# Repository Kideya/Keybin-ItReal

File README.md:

# Keybin-ItReal
A repo for sharing my keyboard designs with the world. Disclaimer: Use at your own risk!

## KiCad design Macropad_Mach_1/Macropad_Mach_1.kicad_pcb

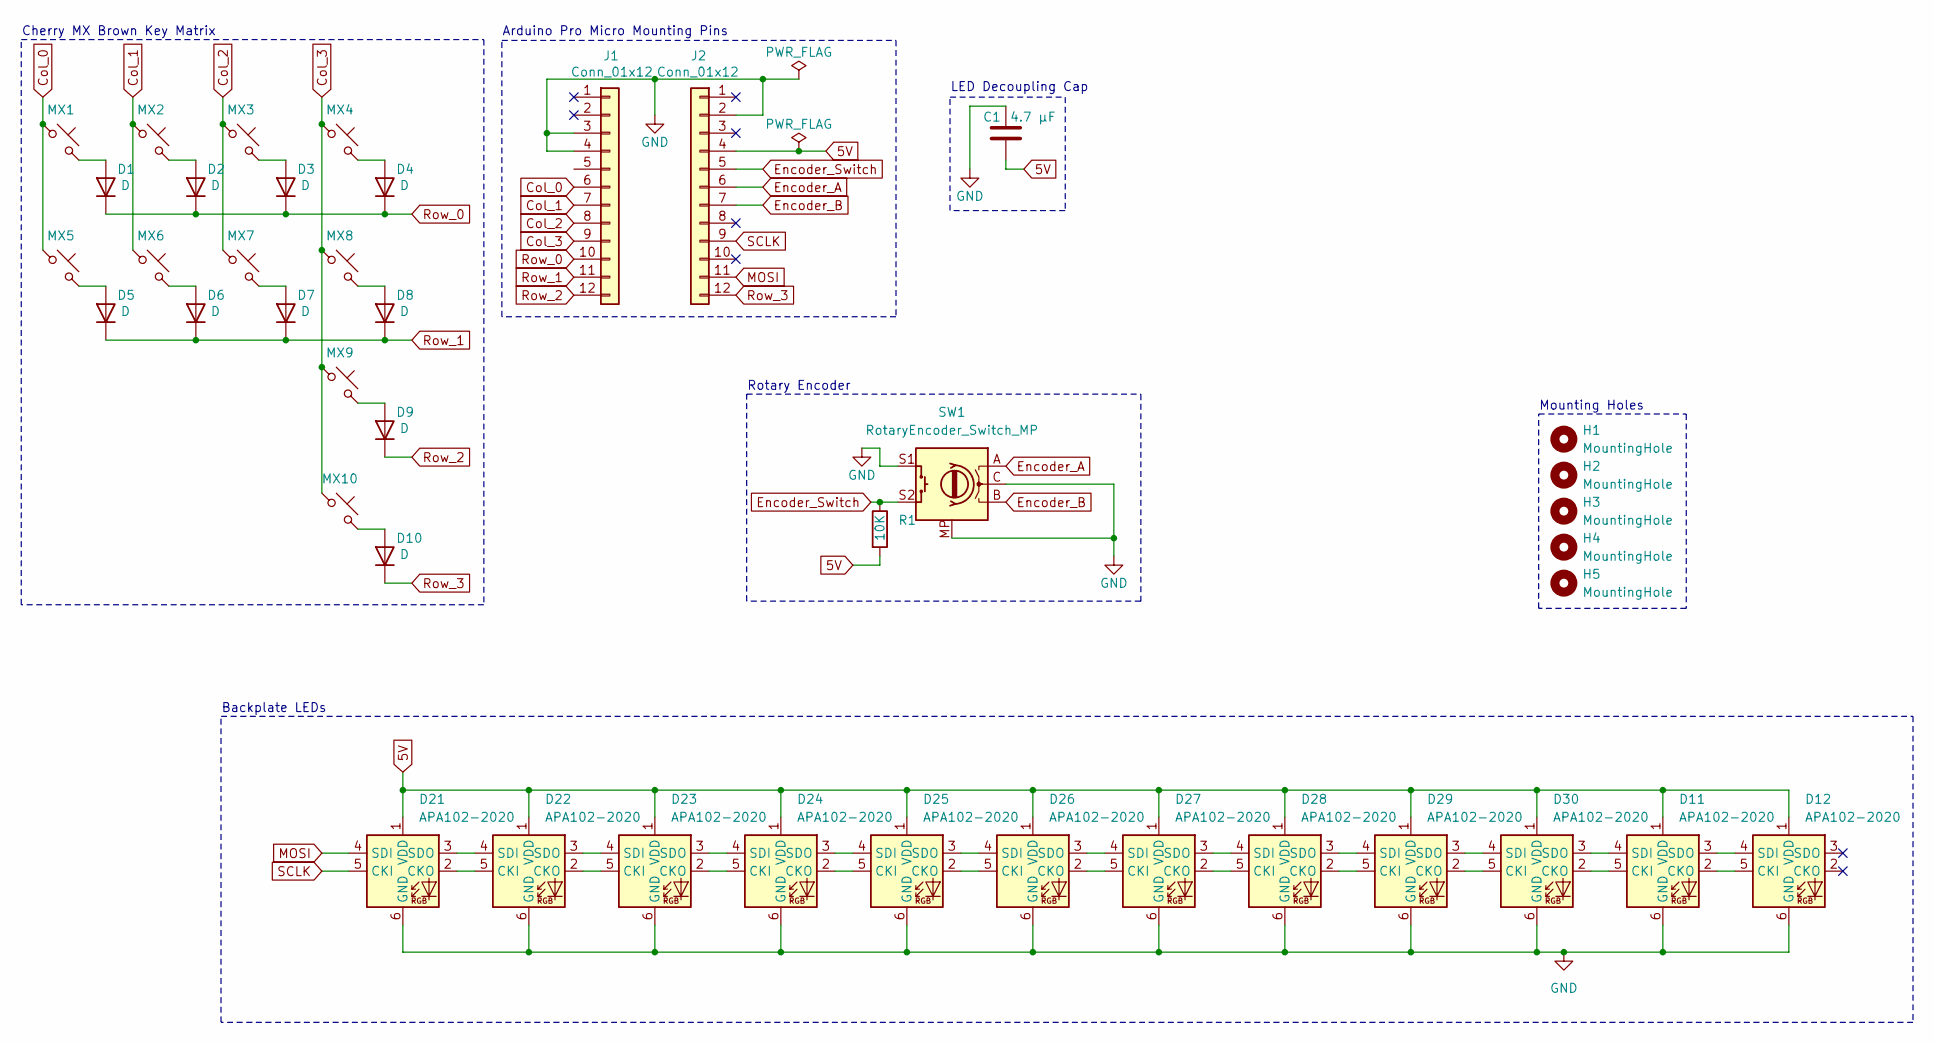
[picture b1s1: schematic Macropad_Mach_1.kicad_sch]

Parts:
C1: 4.7 µF; C_0201_0603Metric_Pad0.64x0.40mm_HandSolder
D1, D2, D3, D4, D5, D6, D7, D8, D9, D10: D; D_A-405_P7.62mm_Horizontal
D11, D12, D21, D22, D23, D24, D25, D26, D27, D28, D29, D30: APA102-2020; LED-APA102-2020
H1, H2, H3, H4, H5: MountingHole; MountingHole_3.2mm_M3
J1, J2: Conn_01x12; PinHeader_1x12_P2.54mm_Vertical
MX1, MX2, MX3, MX4, MX5, MX6, MX7, MX8, MX9, MX10: MX_SW_solder; SW_MX_1u
R1: 10K; R_0603_1608Metric_Pad0.98x0.95mm_HandSolder
SW1: RotaryEncoder_Switch_MP; RotaryEncoder_Alps_EC12E-Switch_Vertical_H20mm

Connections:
5V: C1.2, D11.1 (VDD), D12.1 (VDD), D21.1 (VDD), D22.1 (VDD), D23.1 (VDD), D24.1 (VDD), D25.1 (VDD), D26.1 (VDD), D27.1 (VDD), D28.1 (VDD), D29.1 (VDD), D30.1 (VDD), J2.4, R1.2
Col_0: J1.6, MX1.1, MX5.1
Col_1: J1.7, MX2.1, MX6.1
Col_2: J1.8, MX3.1, MX7.1
Col_3: J1.9, MX4.1, MX8.1, MX9.1, MX10.1
Encoder_A: J2.6, SW1.A
Encoder_B: J2.7, SW1.B
Encoder_Switch: J2.5, R1.1, SW1.S2
GND: C1.1, D11.6 (GND), D12.6 (GND), D21.6 (GND), D22.6 (GND), D23.6 (GND), D24.6 (GND), D25.6 (GND), D26.6 (GND), D27.6 (GND), D28.6 (GND), D29.6 (GND), D30.6 (GND), J1.3, J1.4, J2.2, SW1.C, SW1.MP, SW1.S1
MOSI: D21.4 (SDI), J2.11
unnamed: D1.2 (A), MX1.2
unnamed: D2.2 (A), MX2.2
unnamed: D3.2 (A), MX3.2
unnamed: D4.2 (A), MX4.2
unnamed: D5.2 (A), MX5.2
unnamed: D6.2 (A), MX6.2
unnamed: D7.2 (A), MX7.2
unnamed: D8.2 (A), MX8.2
unnamed: D9.2 (A), MX9.2
unnamed: D10.2 (A), MX10.2
unnamed: D11.5 (CKI), D30.2 (CKO)
unnamed: D11.2 (CKO), D12.5 (CKI)
unnamed: D11.4 (SDI), D30.3 (SDO)
unnamed: D11.3 (SDO), D12.4 (SDI)
unnamed: D21.2 (CKO), D22.5 (CKI)
unnamed: D21.3 (SDO), D22.4 (SDI)
unnamed: D22.2 (CKO), D23.5 (CKI)
unnamed: D22.3 (SDO), D23.4 (SDI)
unnamed: D23.2 (CKO), D24.5 (CKI)
unnamed: D23.3 (SDO), D24.4 (SDI)
unnamed: D24.2 (CKO), D25.5 (CKI)
unnamed: D24.3 (SDO), D25.4 (SDI)
unnamed: D25.2 (CKO), D26.5 (CKI)
unnamed: D25.3 (SDO), D26.4 (SDI)
unnamed: D26.2 (CKO), D27.5 (CKI)
unnamed: D26.3 (SDO), D27.4 (SDI)
unnamed: D27.2 (CKO), D28.5 (CKI)
unnamed: D27.3 (SDO), D28.4 (SDI)
unnamed: D28.2 (CKO), D29.5 (CKI)
unnamed: D28.3 (SDO), D29.4 (SDI)
unnamed: D29.2 (CKO), D30.5 (CKI)
unnamed: D29.3 (SDO), D30.4 (SDI)
Row_0: D1.1 (K), D2.1 (K), D3.1 (K), D4.1 (K), J1.10
Row_1: D5.1 (K), D6.1 (K), D7.1 (K), D8.1 (K), J1.11
Row_2: D9.1 (K), J1.12
Row_3: D10.1 (K), J2.12
SCLK: D21.5 (CKI), J2.9

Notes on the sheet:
Arduino Pro Micro Mounting Pins
Backplate LEDs
Cherry MX Brown Key Matrix
Mounting Holes
LED Decoupling Cap
Rotary Encoder

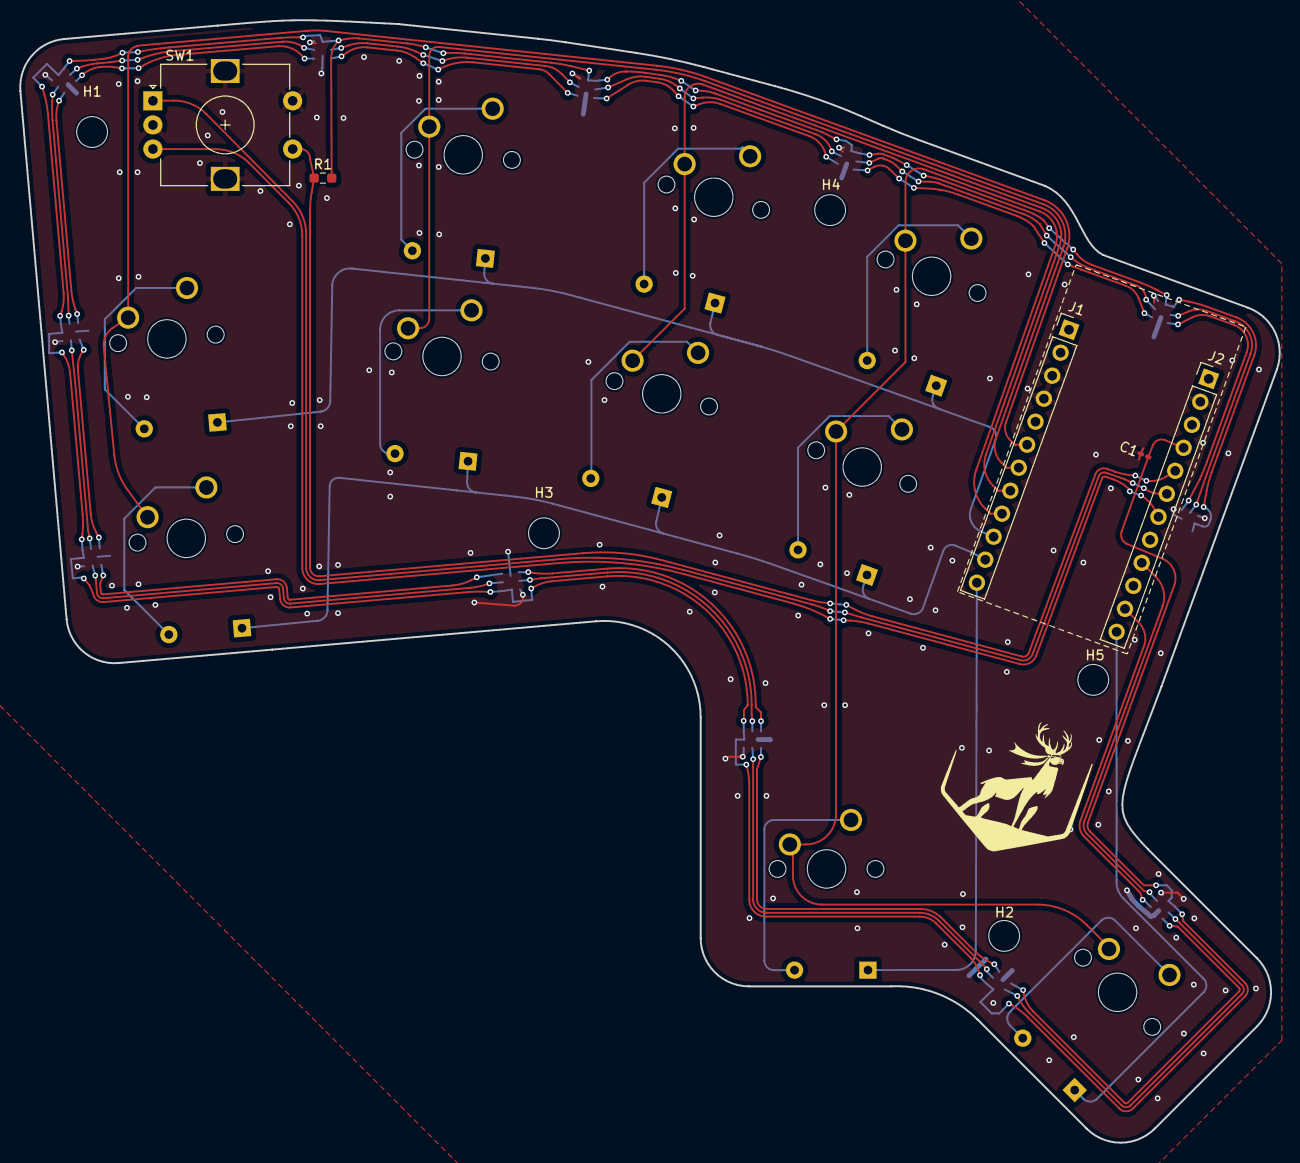
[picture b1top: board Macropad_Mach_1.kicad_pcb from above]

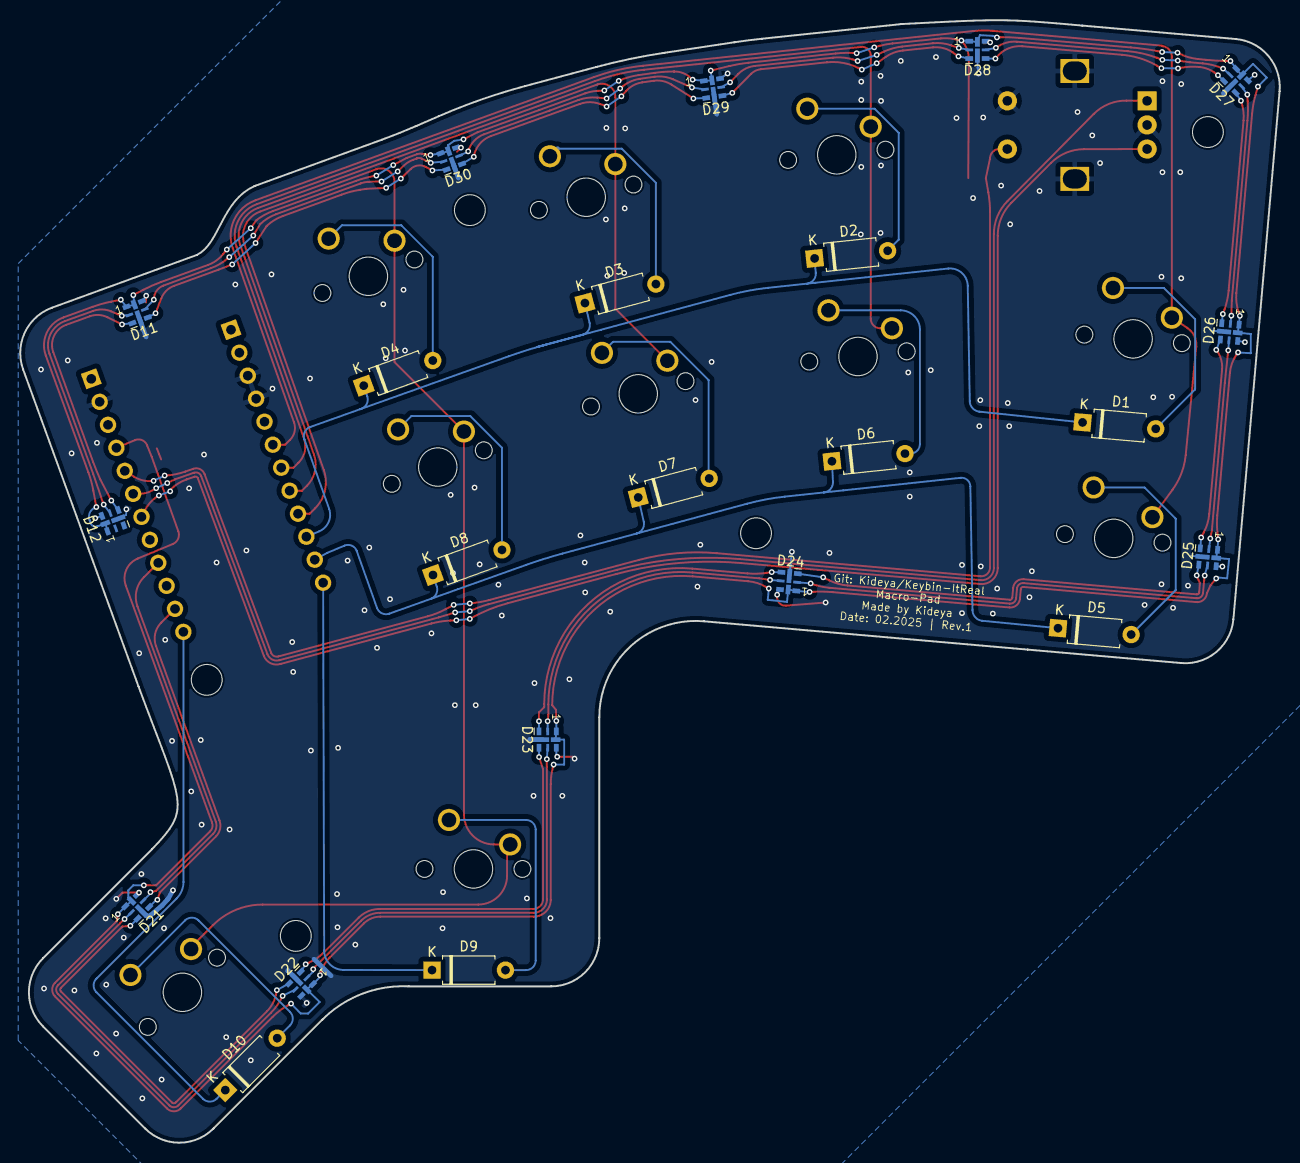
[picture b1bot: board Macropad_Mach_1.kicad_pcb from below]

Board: 2 copper layers, 130.7 x 116.5 mm, 42 parts (22 on the bottom side), 47 nets.

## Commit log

2025-01-29 added files for the Macropad_Mach_1
2025-01-29 fixed folder hirarchy
2025-01-29 feat: update PCB with APA102-2020 LEDs, keyboard layout, and encoder
    - Replaced LEDs with APA102-2020
    - Created the keyboard layout
    - Added Edgecuts
    - Routed the keys
    - Integrated the encoder into the layout
2025-02-03 Finalized PCB routing, connected decoder, and improved design for manufacturing
    - Completed trace routing for the keys
    - Connected the decoder to the circuit
    - Refined silkscreen for better readability
    - Adjusted trace widths to meet design requirements
    - Optimized clearance settings for JLCPCB manufacturing
2025-02-10 Feat: added Logoand Description
